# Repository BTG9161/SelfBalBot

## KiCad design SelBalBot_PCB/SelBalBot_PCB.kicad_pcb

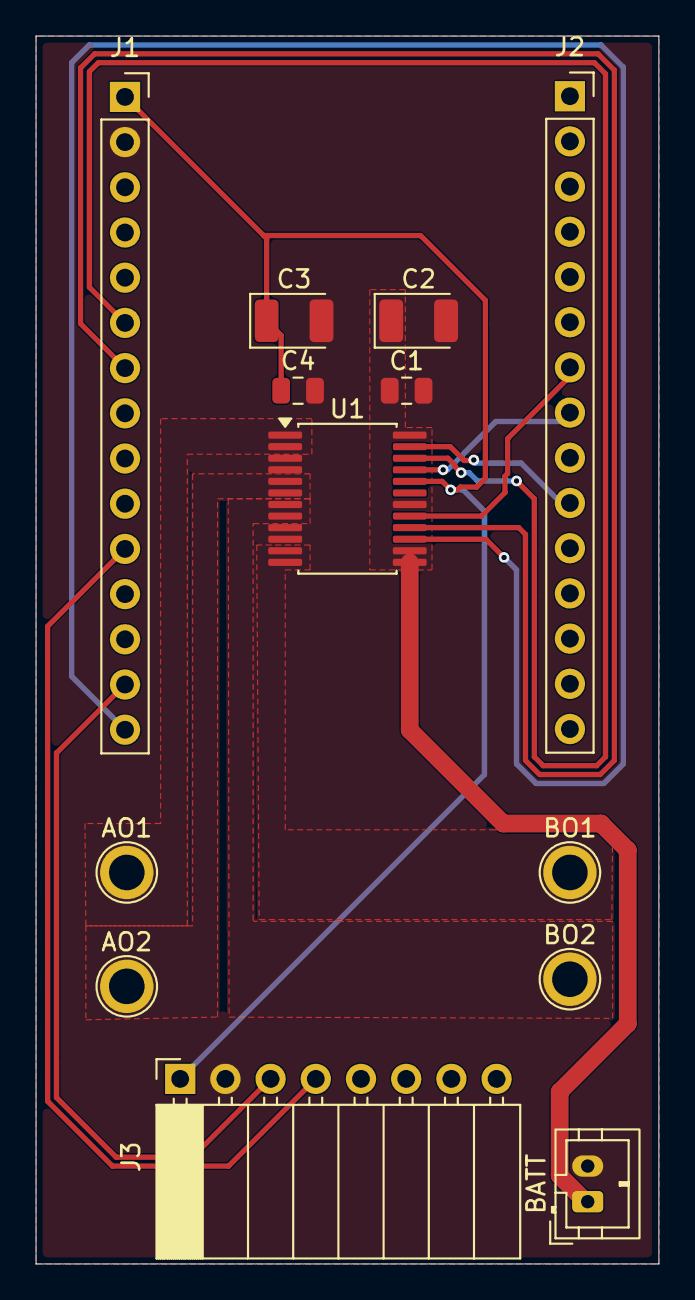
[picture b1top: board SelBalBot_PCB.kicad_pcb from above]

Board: 2 copper layers, 35.0 x 69.0 mm, 13 parts (0 on the bottom side), 15 nets.

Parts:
AO1, AO2: TestPoint_Plated_Hole_D2.0mm
BATT: JST_PH_B2B-PH-K_1x02_P2.00mm_Vertical
BO1, BO2: TestPoint_Plated_Hole_D2.0mm
C1, C4: 100n; C_0805_2012Metric
C2, C3: 10u; CP_EIA-3528-12_Kemet-T
J1, J2: Conn_01x15_Socket; PinSocket_1x15_P2.54mm_Vertical
J3: Conn_01x08_Socket; PinSocket_1x08_P2.54mm_Horizontal
U1: TB6612FNG; SSOP-24_5.3x8.2mm_P0.65mm

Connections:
/AIN1: J2.8, U1.21 (AIN1)
/AIN2: J1.6, U1.22 (AIN2)
/AO1: AO1.1, U1.1 (AO1), U1.2 (AO1)
/AO2: AO2.1, U1.5 (AO2), U1.6 (AO2)
/BIN1: J2.7, U1.17 (BIN1)
/BIN2: J1.7, U1.16 (BIN2)
/BO1: BO1.1, U1.11 (BO1), U1.12 (BO1)
/BO2: BO2.1, U1.7 (BO2), U1.8 (BO2)
/PWMA: J2.10, U1.23 (PWMA)
/PWMB: J1.15, U1.15 (PWMB)
/SCL: J1.14, J3.3
/SDA: J1.11, J3.4
/VM: BATT.1, C1.1, C2.1, U1.13 (VM2), U1.14 (VM3), U1.24 (VM1)
GND: BATT.2, C1.2, C2.2, C3.2, C4.2, J1.2, J3.2, U1.3 (PGND1), U1.4 (PGND1), U1.9 (PGND2), U1.10 (PGND2), U1.18 (GND)
VCC: C3.1, C4.1, J1.1, J3.1, U1.20 (VCC)

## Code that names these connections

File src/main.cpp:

#include <Arduino.h>
#include <Wire.h>
#include <WiFi.h>
#include "Adafruit_MPU6050.h"
#include <madgwickFilter.h>


#define AIN1  25
#define BIN1  26

#define AIN2  16
#define BIN2  17

#define PWMA 32
#define PWMB 23

#define CH_A 0
#define CH_B 1


Adafruit_MPU6050 mpu;
WiFiClient client;
WiFiServer server(8080);
sensors_event_t a, g, temp;

const char* ssid = "DRONE_WIFI";
const char* pass = "12345678";

bool armed = false;
bool Connected = false;

char c;

float ax, ay, az;
float gx, gy, gz;

int InputPitch;

float pitch;
float ratePitch;
float ErrorPitch;

float PRatePitch;
float IRatePitch;
float DRatePitch;

float PID_Return [] = {0, 0, 0};
float PrevErrorPitch;
float PrevItermPitch;


void PID(float Error, float P, float I, float D ,float PrevError, float PrevIterm, float dt){
  float Pterm = P * Error;
  
  float Iterm = PrevIterm + I * (Error + PrevError) * dt * 0.5f;
  Iterm = constrain(Iterm, -400, 400);

  float Dterm = -D * ratePitch;

  float PID_Output = Pterm + Iterm + Dterm;
  PID_Output = constrain(PID_Output, -400, 400);

  PID_Return[0] = PID_Output;
  PID_Return[1] = Error;
  PID_Return[2] = Iterm;
}

void setMotor(int in1, int in2, int channel, int speed) {
  if (speed >= 0) {
    digitalWrite(in1, HIGH);
    digitalWrite(in2, LOW);
    ledcWrite(channel, speed);
  } else if (speed < 0) {
    digitalWrite(in1, LOW);
    digitalWrite(in2, HIGH);
    ledcWrite(channel, -speed);
  }
}

void mixMotors(int pitchPID) {
  int mA = pitchPID;
  int mB = pitchPID;

  // Normalize instead of brutal clipping
  int maxMotor = max(abs(mA), abs(mB));

  if (maxMotor > 255) {
    int excess = maxMotor - 255;
    mA -= excess;
    mB -= excess;
  }

  // Lower bound safety
  mA = constrain(mA, -255, 255);
  mB = constrain(mB, -255, 255);

  setMotor(AIN1, AIN2, CH_A, mA);
  setMotor(BIN1, BIN2, CH_B, mB);
}

void setup() {
  Serial.begin(115200);
  Wire.begin(21, 22);
  Wire.setClock(400000);
  mpu.begin();

  WiFi.mode(WIFI_AP);
  WiFi.softAP(ssid, pass);
  Serial.print("IP: ");
  Serial.println(WiFi.softAPIP());
  server.begin();

  pinMode(AIN1, OUTPUT); pinMode(AIN2, OUTPUT);
  pinMode(BIN1, OUTPUT); pinMode(BIN2, OUTPUT);

  //pinMode(STBY, OUTPUT);
  //digitalWrite(STBY, HIGH); // Enable driver, can be later used for arming or disarming the quadcopter

  // PWM setup
  ledcSetup(CH_A, 20000, 8);
  ledcSetup(CH_B, 20000, 8);

  ledcAttachPin(PWMA, CH_A);
  ledcAttachPin(PWMB, CH_B);
}

void loop() {
  //Calculates dt
  static unsigned long lastTime;
  unsigned long now = micros();

  if (lastTime == 0) {
    lastTime = now;
    return;
  }
  
  float dt = (now - lastTime) / 1000000.0f;
  lastTime = now;
  if (dt <= 0 || dt > 0.1f) dt = 0.01f;


  //Reading data
  if (!client || !client.connected()) {
    client = server.available();
  }
  if (client && client.connected()) {
    Serial.println("Connection Successful");
    Connected = true;

    while (client.available()) {
      int val = client.read();
      
      if (val != -1) {
        c = (char)val;
        Serial.print(c);

        if (c == 'W') {
          InputPitch += 100;
        }
        else if (c == 'S') {
          InputPitch -= 100;
        }
        else if (c == 'X') {
          armed = true;
        }
        else if (c == 'Z') {
          armed = false;
        }
      }
    }
  }

  if (!armed || !Connected) {
    mixMotors(0);
    return;
  }
  if (c == 'Q'){
    client.stop();
  }
  
  //Mapping and converting data to desired formats
  pitch = map(InputPitch, 0, 1023, -20, 20);

  mpu.getEvent(&a, &g, &temp);
  
  ax = a.acceleration.x;
  ay = a.acceleration.y;
  az = a.acceleration.z;

  gx = g.gyro.x;
  gy = g.gyro.y;
  gz = g.gyro.z;

  ratePitch = gy * 57.2958;
    
  // Update Madgwick filter
  imu_filter(ax, ay, az, gx, gy, gz, dt);

  float m_roll = 0;
  float m_pitch = 0;
  float m_yaw = 0;

  eulerAngles(q_est, &m_roll, &m_pitch);
  
  ErrorPitch = pitch - m_pitch;
  
  PID(ErrorRatePitch, PRatePitch, IRatePitch, DRatePitch, PrevErrorPitch, PrevItermPitch, dt);
  float pitchPID = PID_Return[0];
  PrevErrorPitch = PID_Return[1];
  PrevItermPitch = PID_Return[2];

  mixMotors((int)pitchPID);

}
